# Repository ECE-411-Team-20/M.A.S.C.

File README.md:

# Project M.A.S.C.
Practicum Project

Mask to Actively Shield from COVID (M.A.S.C.)

A face shield of some type (either head or collar mounted) that exposes the face by default, but should the wearer start to walk, or should someone approach the user, the face shield moves to cover the wearer's face

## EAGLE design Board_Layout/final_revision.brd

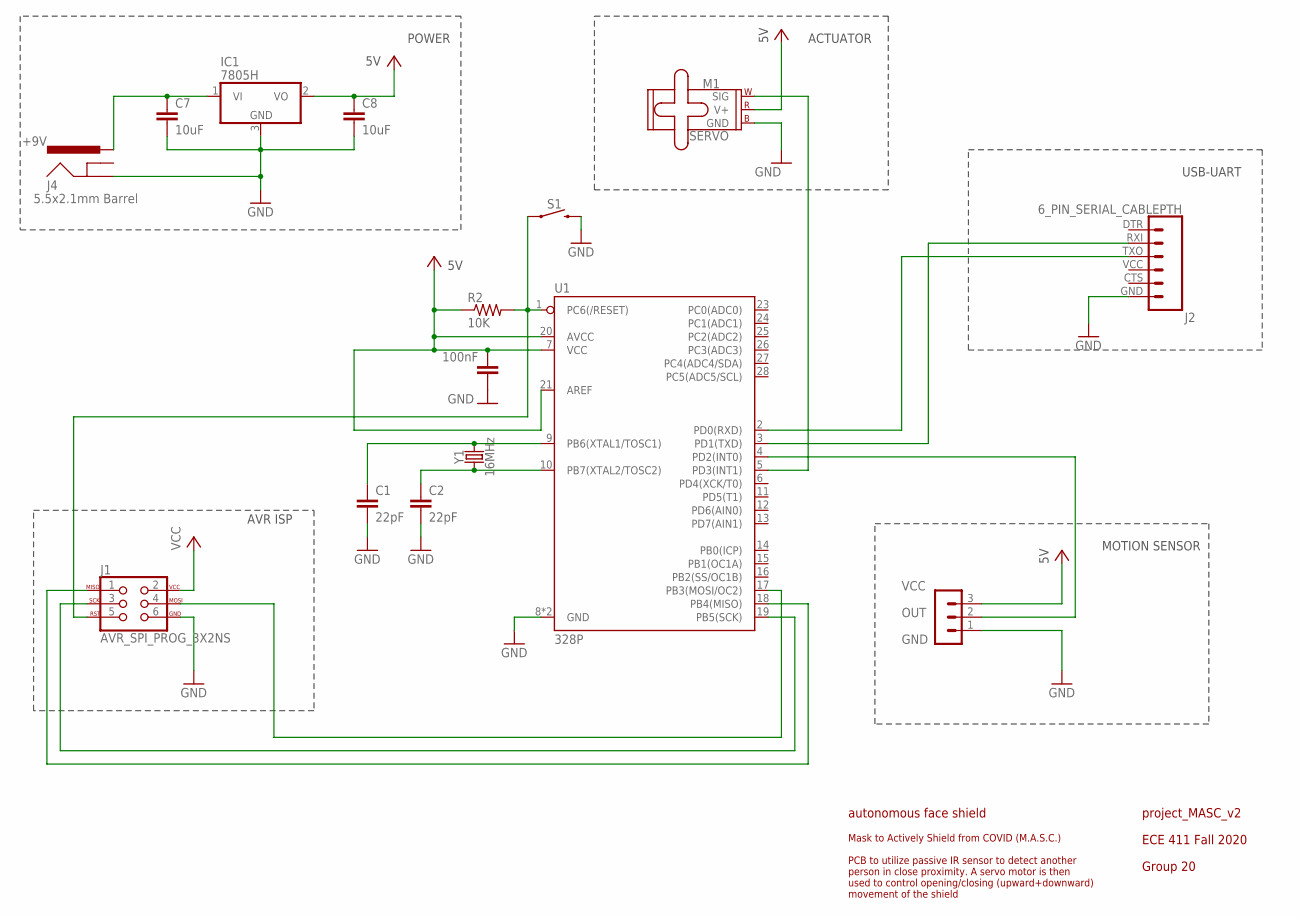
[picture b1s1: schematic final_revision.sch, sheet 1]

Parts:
C1, C2: 22pF; 0805
C3: 100nF; 0805
C7, C8: 10uF; 0805
IC1: 7805H; TO39
J1: AVR_SPI_PROG_3X2NS; 2X3-NS
J2: 6_PIN_SERIAL_CABLEPTH; FTDI_BASIC
J4: 5.5x2.1mm Barrel; POWER_JACK_SMD
M1: SERVO; 1X03
R2: 10K; R0805
S1: MOMENTARY-SWITCH-SPST-PTH-6.0MM; TACTILE_SWITCH_PTH_6.0MM
SV1: MA03-1
U1: 328P; DIP28
Y1: 16MHz; HC49US

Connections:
GND: C1.2, C2.2, C3.1, C7.2, C8.2, IC1.3 (GND), J1.6, J2.GND (6), J4.P$4 (GND), M1.3 (GND), S1.3 (2), SV1.1, U1.8 (GND), U1.22 (GND)
unnamed: J1.5, R2.2, S1.1, U1.1 (PC6(/RESET))
unnamed: J2.TXO (3), U1.2 (PD0(RXD))
unnamed: J2.RXI (2), U1.3 (PD1(TXD))
unnamed: C1.1, U1.9 (PB6(XTAL1/TOSC1)), Y1.2
unnamed: C2.1, U1.10 (PB7(XTAL2/TOSC2)), Y1.1
unnamed: C7.1, IC1.1 (VI), J4.VIN0 (PWR)
unnamed: SV1.2, U1.4 (PD2(INT0))
unnamed: M1.1 (SIG), U1.5 (PD3(INT1))
unnamed: J1.3, U1.19 (PB5(SCK))
unnamed: J1.1, U1.18 (PB4(MISO))
unnamed: J1.4, U1.17 (PB3(MOSI/OC2))
VCC: C3.2, C8.1, IC1.2 (VO), J1.2, M1.2 (V+), R2.1, SV1.3, U1.7 (VCC), U1.20 (AVCC), U1.21 (AREF)

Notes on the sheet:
POWER
ACTUATOR
MOTION SENSOR
USB-UART
AVR ISP
project_MASC_v2
autonomous face shield
Mask to Actively Shield from COVID (M.A.S.C.) PCB to utilize passive IR sensor to detect another person in close proximity. A servo motor is then used to control opening/closing (upward+downward) movement of the shield
Group 20
ECE 411 Fall 2020
+9V
VCC
OUT
GND

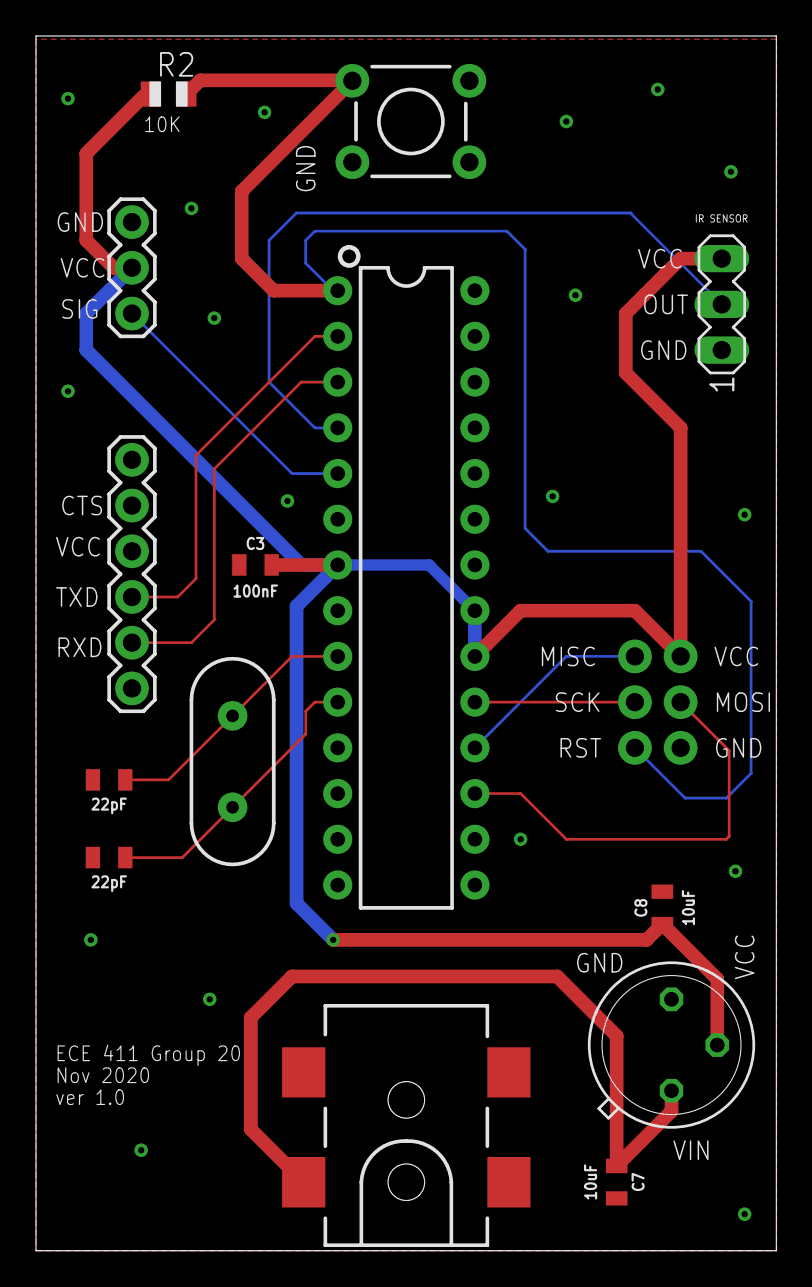
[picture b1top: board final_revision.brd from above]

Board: 2 copper layers, 41.1 x 67.5 mm, 15 parts (0 on the bottom side), 13 nets.

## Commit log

2020-10-26 Added PDS file
2020-11-01 Adding first schematic drafts
2020-11-02 Uploading breadboard prototype files
2020-11-04 Added MASC Arduino sketch WIP
    So far I've only added the ability to read the acceleromter/gyroscope into memory.
    Still need:
    -Read Passive InfraRed Sensor, store in memory.
    -Create logic structure which checks acceleration and infrared motion.
    -Control Servo based on input.
    Pins were based off the ATMega328P Pinout Mapping that I've also posted on Git.
2020-11-04 Added ATMega328P pinout
    Used in determining pins in code.
2020-11-08 Revised schematic and board layout
    Made changes to schematic
    Made changes to board layout to include a barrel jack connector
2020-11-08 Adding snapshots of board
2020-11-08 Uploading v2 layout pdf
2020-11-16 Pushing_updated_schematic_board_files
2020-11-22 committing cleanup branch
2020-11-22 final cleanup
2020-12-04 Adding final commit screenshots

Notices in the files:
parts and their libraries:
SparkFun-Capacitors: Licensing: Creative Commons ShareAlike 4.0 International - https://creativecommons.org/licenses/by-sa/4.0
